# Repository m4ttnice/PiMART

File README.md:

# PiMART

## Introducción
Proyecto del equipo MART para la temporada 2020/2021 de Formula Student. Se pretende diseñar un sistema de telemetría basado en una Rasberry-Pi.

## Conceptos previos

El sistema debe poseer las siguientes características, ordenadas por prioridad:

1. [x] **RTC** (ds3231) para el RPI. La raspberry no tiene integrado reloj del sistema, para sistemas "aislados" se necesita añadir uno para tener un reloj sincronizado (dato indispensable para un sistema de telemetría). Utiliza bus i2c (0x68)
1. [x] Bus **i2c** en el **RPI** (pruebas con RTC (ds3231 0x68) y IMU (mpu6050 0x69))
1. [ ] (**WIP**) **i2c** para **C/C++** en la RPI (pruebas con RTC (ds3231) y IMU (mpu6050))
1. [ ] Capacidad de recepción/transmisión mediante bus **CAN**, para comunicación con la **ECU**.
1. [ ] **GPS** + **IMU** (proporcionados por TORSA) (DETERMINAR **MODELO y LIBRERÍAS** A UTILIZAR) (con un enlace al **datasheet** basta por ahora)
1. [ ] **RPI** definitiva (proporcionados por TORSA) (DETERMINAR **MODELO, SO y CARACTERÍSTICAS** A UTILIZAR)
1. [ ] Almacenamiento de datos recibidos por CAN desde ECU.
1. [ ] Leer, en la RPI, el estado de los *botones del volante* (18), se pueden usar 2 opciones:
    - **Lectura directa**: se cablea cada interruptor a un pin **GPIO** o a una entrada de **multiplexor** y este a GPIO (en ppio más simple en SOFTWARE, más complicado en HARWARE [ **MUCHOS** cables desde el volante al RPI])
    - **Lectura indirecta**: se coloca un microcontrolador en el volante el cuál lee el estado de los botones y lo comunica al RPI mediante un protocolo de comunicacion (pej. I2C, CAN , SPI) (excluyendo los problemas impícitos al protocolo de comunicaciones[distancia max del bus, compatibilidad del sw], esta opcion puede ser la más sencilla de implementar y permite un mayor grado de control)
1. [ ] Procesamiento del estado de los botones,en el RPI. Es decir ejecutar la acción de cada botón pulsado (SET MAX RPM [CAN], CHANGE DASHBOARD [SCREEN], START SAVE DATA [RPI], etc)
1. [ ] **GPS** establecer comunicacion con la placa + almacenar los datos
1. [ ] **IMU** establecer comunicación + procesar/recoger los datos provenientes de la unidad inercial
1. [ ] Pruebas de recepcion de datos a la vel. de muestreo definida
1. [ ] Pruebas de la pantalla. Envio de datos RAW 
1. [ ] Sensor de temperatura **IR** + **Distancia Laser** para las ruedas [x4]. Diseño y pruebas de prototipo.
1. [ ] Vúmetro
1. [ ] Comunicación de los 4 sensores con el RPI. En principio este sensor utiliza bus i2c (ver direcciones , posible necesite multiplexor ó otro método de comunicacion [**VER**])
    - De utilizar bus i2c HAY que utilizar **i2c diferencial** (esta en un entorno RUIDOSO y la distancia del bus es considerable)
1. [ ] Diseño del **GUI** definitivo

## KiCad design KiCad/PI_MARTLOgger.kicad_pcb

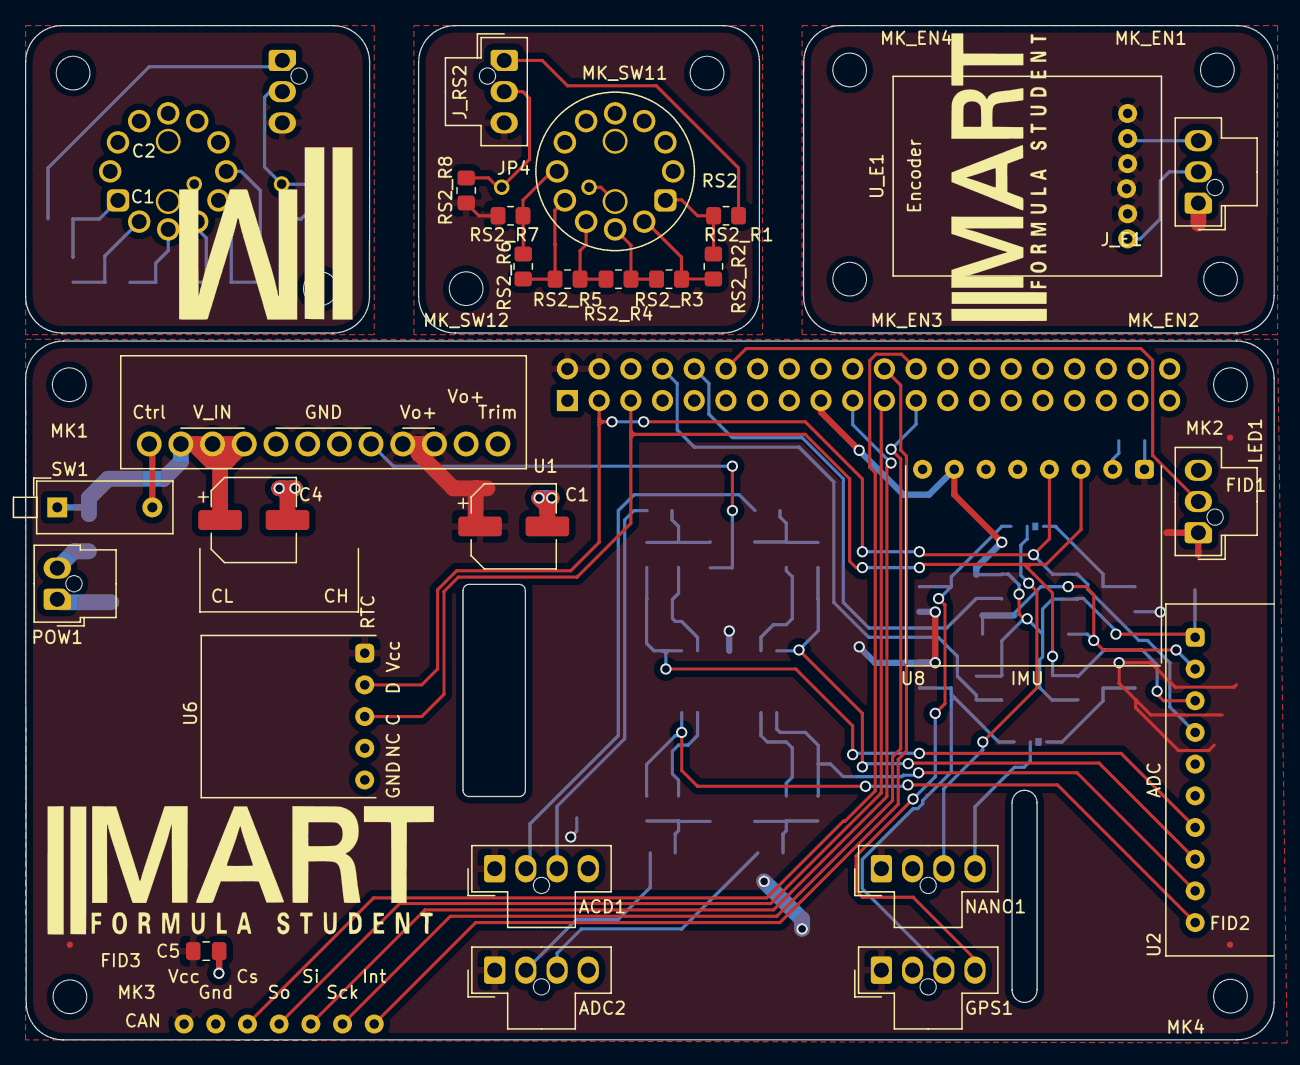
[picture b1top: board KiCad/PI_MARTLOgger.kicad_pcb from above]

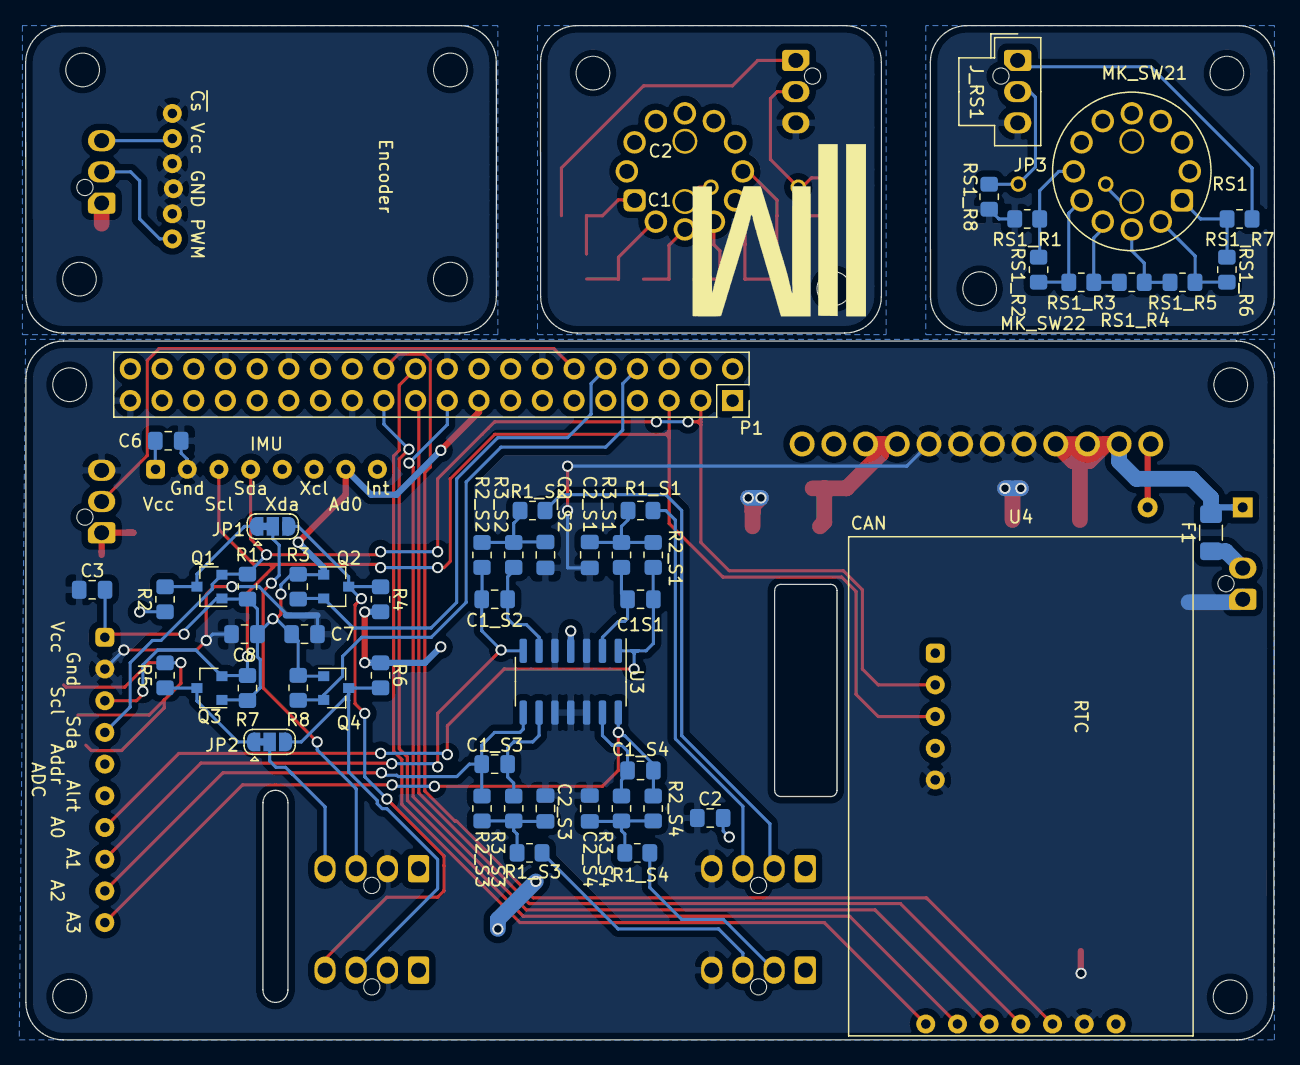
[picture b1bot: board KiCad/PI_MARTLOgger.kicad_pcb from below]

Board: 2 copper layers, 100.1 x 81.3 mm, 96 parts (56 on the bottom side), 61 nets.

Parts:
ACD1: Conn_01x04_Female; Molex_Nano-Fit_105309-xx04_1x04_P2.50mm_Vertical
ADC2: Conn_01x04_Female; Molex_Nano-Fit_105309-xx04_1x04_P2.50mm_Vertical
C1, C4: 100u; CP_Elec_6.3x7.7
C1S1: 1u; C_0805_2012Metric_Pad1.18x1.45mm_HandSolder
C1_S2, C1_S3, C1_S4: C1; C_0805_2012Metric_Pad1.18x1.45mm_HandSolder
C2, C3, C7, C8: 100n; C_0805_2012Metric_Pad1.18x1.45mm_HandSolder
C2_S1: 3.9u; C_0805_2012Metric_Pad1.18x1.45mm_HandSolder
C2_S2, C2_S3, C2_S4: C2; C_0805_2012Metric_Pad1.18x1.45mm_HandSolder
C5, C6: .1u; C_0805_2012Metric_Pad1.18x1.45mm_HandSolder
F1: Fuse; Fuse_1206_3216Metric_Pad1.42x1.75mm_HandSolder
FID1, FID2, FID3: Fiducial; Fiducial_0.5mm_Mask1.5mm
GPS1: GPS; Molex_Nano-Fit_105309-xx04_1x04_P2.50mm_Vertical
JP1, JP2: SolderJumper_3_Bridged12; SolderJumper-3_P1.3mm_Bridged12_RoundedPad1.0x1.5mm
JP3, JP4: Jumper; Bridge_7mm
J_E1: Conn_01x03_Female; Molex_Nano-Fit_105309-xx03_1x03_P2.50mm_Vertical
J_RS1, J_RS2: Conn_01x03_Female; Molex_Nano-Fit_105309-xx03_1x03_P2.50mm_Vertical
LED1: Vumetro; Molex_Nano-Fit_105309-xx03_1x03_P2.50mm_Vertical
MK1, MK2, MK3, MK4: M2.5; MountingHole_2.7mm_M2.5
MK_EN1, MK_EN2, MK_EN3, MK_EN4: M2.5; MountingHole_2.7mm_M2.5
MK_SW11, MK_SW12, MK_SW21, MK_SW22: M2.5; MountingHole_2.7mm_M2.5
NANO1: Nano (I2c-UART); Molex_Nano-Fit_105309-xx04_1x04_P2.50mm_Vertical
P1: Conn_02x20_Odd_Even; PinSocket_2x20_P2.54mm_Vertical
POW1: Con. Bateria; Molex_Nano-Fit_105309-xx02_1x02_P2.50mm_Vertical
Q1, Q2, Q3, Q4: BSS138; SOT-23
R1, R2, R3, R4, R5, R6, R7, R8: 10k; R_0805_2012Metric_Pad1.20x1.40mm_HandSolder
R1_S1, R3_S1: 5.1k; R_0805_2012Metric_Pad1.20x1.40mm_HandSolder
R1_S2, R1_S3, R1_S4: R1; R_0805_2012Metric_Pad1.20x1.40mm_HandSolder
R2_S1: 3.3k; R_0805_2012Metric_Pad1.20x1.40mm_HandSolder
R2_S2, R2_S3, R2_S4: R2; R_0805_2012Metric_Pad1.20x1.40mm_HandSolder
R3_S2, R3_S3, R3_S4: R3; R_0805_2012Metric_Pad1.20x1.40mm_HandSolder
RS1, RS2: RotSwitch; Rot_Switch
RS1_R1, RS1_R2, RS1_R3, RS1_R4, RS1_R5, RS1_R6, RS1_R7, RS2_R1, RS2_R2, RS2_R3, RS2_R4, RS2_R5, RS2_R6, RS2_R7: 2.2k; R_0805_2012Metric_Pad1.20x1.40mm_HandSolder
RS1_R8, RS2_R8: 220k; R_0805_2012Metric_Pad1.20x1.40mm_HandSolder
SW1: SW_DIP_x01; SW_DIP_SPSTx01_Piano_10.8x4.1mm_W7.62mm_P2.54mm
U1: CC-CC_P783S; CC-CC_PT83-S
U2: ADC
U3: LM324; SOIC-14_3.9x8.7mm_P1.27mm
U4: CAN
U6: RTC
U8: IMU
U_E1: Encoder

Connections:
+3V3: C3.1, C7.1, C8.1, P1.17, Q1.1, Q2.1, Q3.1, Q4.1, R1.1, R3.1, R7.1, R8.1, U2.1, U8.7
+5V: ACD1.1, ADC2.1, C1.1, C2.1, C5.1, C6.1, GPS1.1, LED1.1, NANO1.1, P1.2, P1.4, R2.1, R4.1, R5.2, R6.2, U1.9, U1.10, U3.4, U4.1, U6.5, U8.1
/A0: C1S1.2, R2_S1.2, U2.7, U3.1
/A1: C1_S2.2, R2_S2.2, U2.8, U3.7
/A2: C1_S3.2, R2_S3.2, U2.9, U3.8
/A3: C1_S4.2, R2_S4.2, U2.10, U3.14
/GPIO2(SDA1): P1.3, Q1.2, R1.2, U2.4, U6.4, U8.4
/GPIO3(SCL1): P1.5, Q3.2, R7.2, U2.3, U6.3, U8.3
/GPIO8(SPI0_CE_N): P1.24, U4.3
/GPIO9(SPI0_MISO): P1.21, U4.4
/GPIO10(SPI0_MOSI): P1.19, U4.5
/GPIO11(SPI0_SCK): P1.23, U4.6
/GPIO14(TXD0): P1.8, Q4.2, R8.2
/GPIO15(RXD0): P1.10, Q2.2, R3.2
/GPIO18(GEN1)(PWM0): LED1.2, P1.12
/GPIO25(GEN6): P1.22, U4.7
/PCBs/E_D: J_E1.2, U_E1.1
/PCBs/E_Gnd: J_E1.1, U_E1.2, U_E1.3, U_E1.4, U_E1.6
/PCBs/E_Vcc: J_E1.3, U_E1.5
/PCBs/RS1_D: JP3.2, J_RS1.2, RS1_R8.2
/PCBs/RS1_Gnd: J_RS1.3, RS1_R1.2, RS1_R8.1
/PCBs/RS1_Vcc: J_RS1.1, RS1_R7.1
/PCBs/RS2_D: JP4.2, J_RS2.2, RS2_R8.2
/PCBs/RS2_Gnd: J_RS2.3, RS2_R7.2, RS2_R8.1
/PCBs/RS2_Vcc: J_RS2.1, RS2_R1.1
/RX_HV: GPS1.4, JP1.3, Q2.3, R4.2
/SCL_HV: JP2.1, Q3.3, R5.1
/SDA_HV: JP1.1, Q1.3, R2.2
/TX_HV: GPS1.3, JP2.3, Q4.3, R6.1
GND: ACD1.4, ADC2.4, C1.2, C2.2, C2_S1.2, C2_S2.2, C2_S3.2, C2_S4.2, C3.2, C4.2, C5.2, C6.2, C7.2, C8.2, GPS1.2, LED1.3, NANO1.2, P1.6, P1.14, P1.20, P1.25, P1.30, P1.34, P1.39, POW1.1, U1.5, U1.6, U1.7, U1.8, U2.2, U3.3, U3.5, U3.10, U3.11, U3.12, U4.2, U6.1, U8.2
unnamed: ACD1.2, R1_S2.1
unnamed: ACD1.3, R1_S1.1
unnamed: ADC2.2, R1_S4.1
unnamed: ADC2.3, R1_S3.1
unnamed: C1S1.1, R3_S1.2, U3.2
unnamed: C1_S2.1, R3_S2.2, U3.6
unnamed: C1_S3.1, R3_S3.2, U3.9
unnamed: C1_S4.1, R3_S4.2, U3.13
unnamed: C2_S1.1, R1_S1.2, R2_S1.1, R3_S1.1
unnamed: C2_S2.1, R1_S2.2, R2_S2.1, R3_S2.1
unnamed: C2_S3.1, R1_S3.2, R2_S3.1, R3_S3.1
unnamed: C2_S4.1, R1_S4.2, R2_S4.1, R3_S4.1
unnamed: C4.1, F1.2, SW1.1, U1.2, U1.3, U1.4
unnamed: F1.1, POW1.2
unnamed: JP1.2, NANO1.3
unnamed: JP2.2, NANO1.4
unnamed: JP3.1, RS1.13
unnamed: JP4.1, RS2.13
unnamed: RS1.1, RS1_R6.1, RS1_R7.2
unnamed: RS1.2, RS1_R5.1, RS1_R6.2
unnamed: RS1.3, RS1_R4.1, RS1_R5.2
unnamed: RS1.4, RS1_R3.1, RS1_R4.2
unnamed: RS1.5, RS1_R2.1, RS1_R3.2
unnamed: RS1.6, RS1_R1.1, RS1_R2.2
unnamed: RS2.1, RS2_R1.2, RS2_R2.1
unnamed: RS2.2, RS2_R2.2, RS2_R3.1
unnamed: RS2.3, RS2_R3.2, RS2_R4.1
unnamed: RS2.4, RS2_R4.2, RS2_R5.1
unnamed: RS2.5, RS2_R5.2, RS2_R6.1
unnamed: RS2.6, RS2_R6.2, RS2_R7.1
unnamed: SW1.2, U1.1

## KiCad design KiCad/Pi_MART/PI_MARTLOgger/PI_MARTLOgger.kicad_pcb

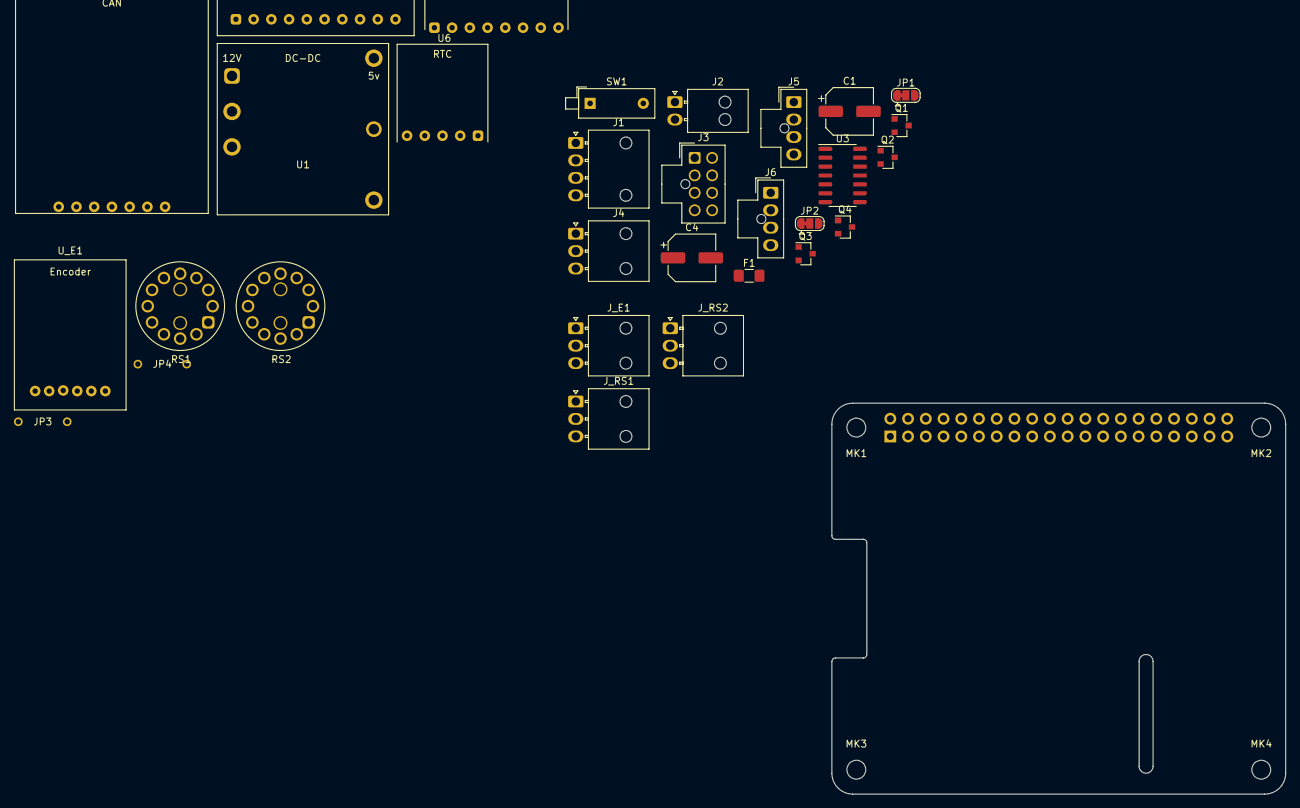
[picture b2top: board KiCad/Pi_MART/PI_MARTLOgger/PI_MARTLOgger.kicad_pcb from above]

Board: 2 copper layers, 65.0 x 56.0 mm, 35 parts (1 on the bottom side), 33 nets, no tracks yet.

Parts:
C1, C4: 100u; CP_Elec_6.3x7.7
F1: Fuse; Fuse_1206_3216Metric_Pad1.42x1.75mm_HandSolder
J1: Nano (I2c-UART); Molex_Nano-Fit_105313-xx04_1x04_P2.50mm_Horizontal
J2: Con. Bateria; Molex_Nano-Fit_105313-xx02_1x02_P2.50mm_Horizontal
J3: GPS; Molex_Nano-Fit_105310-xx08_2x04_P2.50mm_Vertical
J4: Vumetro; Molex_Nano-Fit_105313-xx03_1x03_P2.50mm_Horizontal
J5, J6: Conn_01x04_Female; Molex_Nano-Fit_105309-xx04_1x04_P2.50mm_Vertical
JP1, JP2: SolderJumper_3_Bridged12; SolderJumper-3_P1.3mm_Bridged12_RoundedPad1.0x1.5mm
JP3, JP4: Jumper; Bridge_7mm
J_E1: Conn_01x03_Female; Molex_Nano-Fit_105313-xx03_1x03_P2.50mm_Horizontal
J_RS1, J_RS2: Conn_01x03_Female; Molex_Nano-Fit_105313-xx03_1x03_P2.50mm_Horizontal
MK1, MK2, MK3, MK4: M2.5; MountingHole_2.7mm_M2.5
P1: Conn_02x20_Odd_Even; PinSocket_2x20_P2.54mm_Vertical
Q1, Q2, Q3, Q4: BSS138; SOT-23
RS1, RS2: RotSwitch; Rot_Switch
SW1: SW_DIP_x01; SW_DIP_SPSTx01_Piano_10.8x4.1mm_W7.62mm_P2.54mm
U1: DC-DC
U2: ADC
U3: LM324; SOIC-14_3.9x8.7mm_P1.27mm
U4: CAN
U6: RTC
U8: IMU
U_E1: Encoder

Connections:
+3V3: P1.1, P1.17, Q1.1, Q2.1, Q3.1, Q4.1, U2.1, U8.7
+5V: C1.1, J1.1, J3.1, J4.1, J5.1, J6.1, P1.2, P1.4, U1.4, U3.4, U4.1, U6.5, U8.1
/A0: U2.7, U3.1
/A1: U2.8, U3.7
/A2: U2.9, U3.8
/A3: U2.10, U3.14
/GPIO2(SDA1): P1.3, Q1.2, U2.4, U6.4, U8.4
/GPIO3(SCL1): P1.5, Q3.2, U2.3, U6.3, U8.3
/GPIO8(SPI0_CE_N): P1.24, U4.3
/GPIO9(SPI0_MISO): P1.21, U4.4
/GPIO10(SPI0_MOSI): P1.19, U4.5
/GPIO11(SPI0_SCK): P1.23, U4.6
/GPIO14(TXD0): P1.8, Q4.2
/GPIO15(RXD0): P1.10, Q2.2
/GPIO18(GEN1)(PWM0): J4.2, P1.12
/GPIO25(GEN6): P1.22, U4.7
/PCBs/E_D: J_E1.2, U_E1.1
/PCBs/E_Gnd: J_E1.1, U_E1.2, U_E1.3, U_E1.4, U_E1.6
/PCBs/E_Vcc: J_E1.3, U_E1.5
/PCBs/RS1_D: JP3.2, J_RS1.2
/PCBs/RS2_D: JP4.2, J_RS2.2
/RX_HV: J3.4, JP1.3, Q2.3
/SCL_HV: JP2.1, Q3.3
/SDA_HV: JP1.1, Q1.3
/TX_HV: J3.3, JP2.3, Q4.3
GND: C1.2, C4.2, J1.2, J2.1, J3.2, J4.3, J5.4, J6.4, P1.6, P1.9, P1.14, P1.20, P1.25, P1.30, P1.34, P1.39, U1.2, U1.6, U2.2, U3.3, U3.5, U3.10, U3.11, U3.12, U4.2, U6.1, U8.2
unnamed: C4.1, F1.2, SW1.1, U1.3
unnamed: F1.1, J2.2
unnamed: J1.3, JP1.2
unnamed: J1.4, JP2.2
unnamed: JP3.1, RS1.13
unnamed: JP4.1, RS2.13
unnamed: SW1.2, U1.1

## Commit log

2021-02-03 Create GitHub_md_Formats
2021-02-03 Rename GitHub_md_Formats to GitHub_md_Formats.md
2021-02-03 First light
2021-02-04 Config_RPI first organization + RTC + I2C
2021-03-31 Flujos De prueba Can-Bus AD1115 NeoPixel, Data-Format CSV
2021-04-25 Add files via upload
    Cambios minimos (Prueba de funcionamiento del flujo en la segunda raspberry)
2021-04-28 Add files via upload
    Añadido marcha para poder verla y cambio entre dashboards
2021-04-28 Add files via upload
    subida de vd actualizada, la anterior no vale
2021-05-04 Add files via upload
    Actualización Dashboard, valor marcha centrado y template de temperatura sin terminar
2021-05-05 Add files via upload
    Marcha con RPM centrada en dashboard, datos de temperatura, presión de aceite,.. sin conseguir color de fondo para el datos
2021-05-09 Add files via upload
    Añadida foto logo mart en la primera pantalla, se han ajustado los tamaños de los tabs en la segunda pantalla
2021-05-16 Add files via upload
    Añadido color de fondo para rangos de valores de temperatura y presión de aceite
2021-06-11 Add KiCad Project
2021-06-11 Add Matlab-Simscape Simulation ADC filter
2021-06-11 Add Schematics
2021-06-28 Schematics+Gerbers+KiCadFiles
    Update PiMART telemetry system
2021-10-29 Create MART_20-21_Project
